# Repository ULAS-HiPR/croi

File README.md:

# Croí

Croí is the core flight-computer node in [Ogma](https://sean-osullivan.com/projects/ogma/), the University of Limerick Aeronautics Society's modular avionics stack for high-powered rocketry.

## Role

- Coordinates flight state across the 500 kbit/s CAN bus.
- Samples an LSM6DSO32 IMU and MS5607 barometer.
- Records flight data to SPI NOR flash.
- Runs on an STM32F072 and can operate as the stack's central logger.

## Repository

- `hardware/` - KiCad design and manufacturing outputs.
- `firmware/` - embedded firmware, peripheral probes, and tests.
- `schematics.png` - exported schematic overview.

## Status

Rev 1 firmware and hardware bring-up continue on [`ogma/flight-hardening`](https://github.com/ULAS-HiPR/croi/tree/ogma/flight-hardening). Release-candidate firmware builds and software tests pass, but hardware-in-the-loop validation is still underway. Croí is not yet flight-proven.

## Manufacturing support

Rev 1 PCB fabrication was sponsored through [EasyEDA Education](https://easyeda.com/education) and manufactured by [JLCPCB](https://jlcpcb.com/). The board was designed in KiCad and imported into EasyEDA Pro for the sponsorship and manufacturing workflow.

## More information

See the [Ogma project write-up](https://sean-osullivan.com/projects/ogma/) for the complete stack, bring-up work, and current status.

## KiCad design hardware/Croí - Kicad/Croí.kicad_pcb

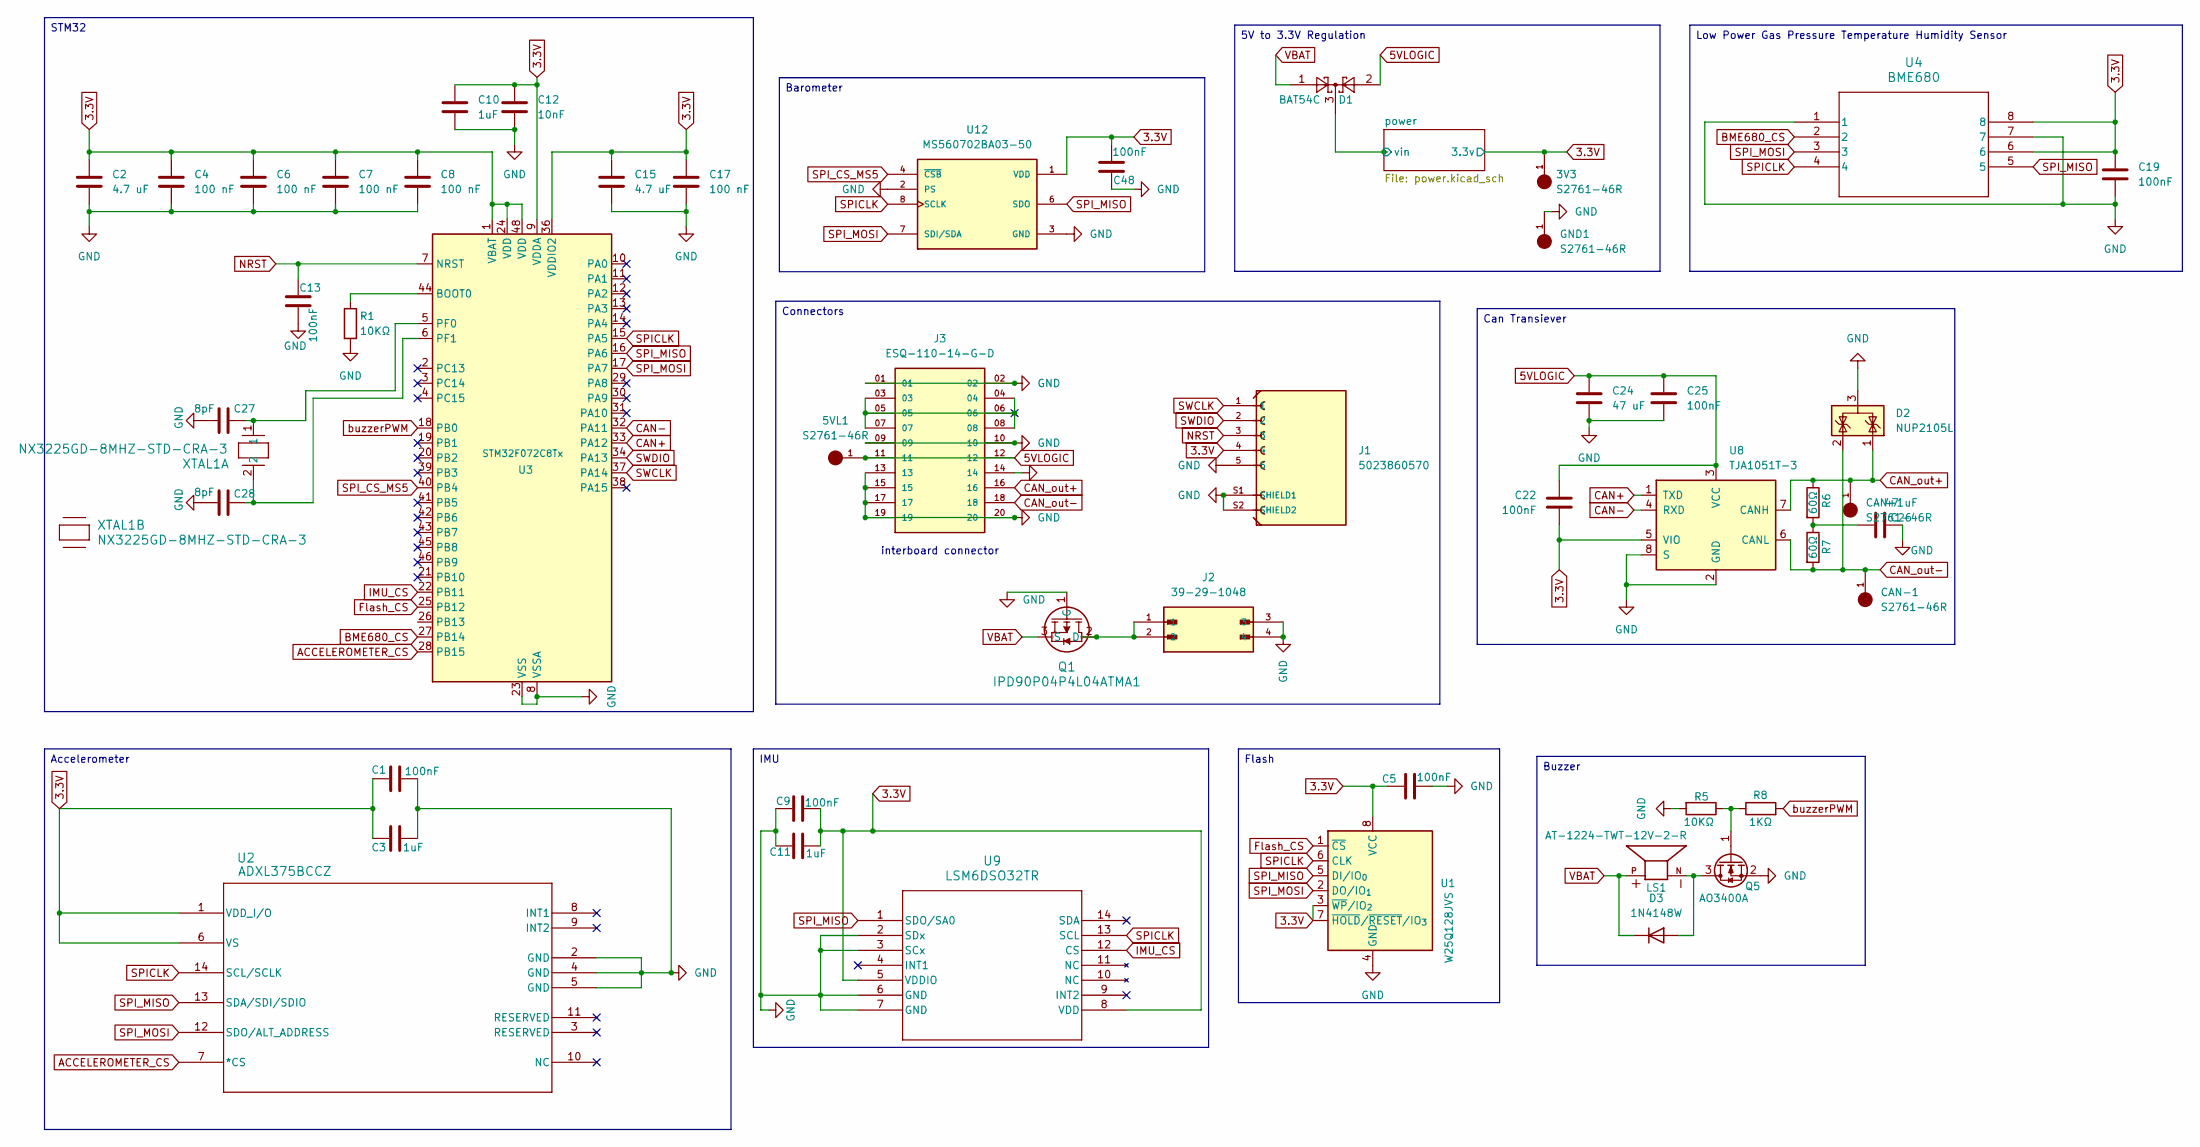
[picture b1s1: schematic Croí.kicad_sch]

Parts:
3V3, 5VL1: S2761-46R; HARWIN_S2761-46R; PARTREV 1
C1, C5, C9, C13, C19, C22, C25: 100nF; C_0402_1005Metric
C2, C15: 4.7 uF; C_0402_1005Metric
C3, C10, C11: 1uF; C_0402_1005Metric
C4, C6, C7, C8, C17: 100 nF; C_0402_1005Metric
C12: 10nF; C_0603_1608Metric
C24, C26: 47 uF; C_0603_1608Metric
C27, C28: 8pF; C_0402_1005Metric
C48: 100nF; R_0402_1005Metric
CAN+1: S2761-46R; HARWIN_S2761-46R; PARTREV 1
CAN-1: S2761-46R; HARWIN_S2761-46R; PARTREV 1
D1: BAT54C; SOT-23
D2: NUP2105L; SOT-23
D3: 1N4148W; D_SOD-123
GND1: S2761-46R; HARWIN_S2761-46R; PARTREV 1
J1: 5023860570; MOLEX_5023860570; PARTREV F
J2: 39-29-1048; MOLEX_39-29-1048
J3: ESQ-110-14-G-D; SAMTEC_ESQ-110-14-G-D; PARTREV NA
LS1: AT-1224-TWT-12V-2-R; XDCR_AT-1224-TWT-12V-2-R; PARTREV 2014/07/25
Q1: IPD90P04P4L04ATMA1; PG-TO252-3-313_INF
Q5: AO3400A; SOT-23
R1, R5: 10KΩ; R_0402_1005Metric
R6, R7: 60Ω; R_0402_1005Metric
R8: 1KΩ; R_0402_1005Metric
U1: W25Q128JVS; SOIC-8_5.3x5.3mm_P1.27mm
U2: ADXL375BCCZ; LGA_CC-14-1_ADI
U3: STM32F072C8Tx; LQFP-48_7x7mm_P0.5mm
U4: BME680; LGA8_BME680_BOS
U8: TJA1051T-3; SOIC-8_3.9x4.9mm_P1.27mm
U9: LSM6DSO32TR; LGA-14L_2P5X3X0P83_STM
U12: MS560702BA03-50; SON125P300X500X100-8N
XTAL1: NX3225GD-8MHZ-STD-CRA-3; XTAL_NX3225GD-8MHZ-STD-CRA-3_NDK

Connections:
3.3V: 3V3.1, C1.1, C2.1, C3.1, C4.1, C5.1, C6.1, C7.1, C8.1, C9.2, C10.1, C11.2, C12.1, C15.1, C17.1, C19.1, C22.1, C48.2, J1.4, U1.3 (~WP/IO_{2}), U1.7 (~HOLD/~RESET/IO_{3}), U1.8 (VCC), U2.1 (VDD_I/O), U2.6 (VS), U3.1 (VBAT), U3.9 (VDDA), U3.24 (VDD), U3.36 (VDDIO2), U3.48 (VDD), U4.6, U4.8, U8.5 (VIO), U9.5 (VDDIO), U9.8 (VDD), U12.1 (VDD); also elsewhere on the board
5VLOGIC: 5VL1.1, C22.2, C24.1, C25.1, D1.2, J3.11, J3.12, U8.3 (VCC); also elsewhere on the board
/power/vin: D1.3; also elsewhere on the board
ACCELEROMETER_CS: U2.7 (*CS), U3.28 (PB15)
BME680_CS: U3.27 (PB14), U4.2
CAN+: U3.33 (PA12), U8.1 (TXD)
CAN-: U3.32 (PA11), U8.4 (RXD)
CAN_out+: CAN+1.1, D2.1 (K), J3.16, R6.1, U8.7 (CANH); also elsewhere on the board
CAN_out-: CAN-1.1, D2.2 (K), J3.18, R7.2, U8.6 (CANL)
Flash_CS: U1.1 (~CS), U3.25 (PB12)
GND: C1.2, C2.2, C3.2, C4.2, C5.2, C6.2, C7.2, C8.2, C9.1, C10.2, C11.1, C12.2, C13.2, C15.2, C17.2, C19.2, C24.2, C25.2, C26.2, C27.1, C28.2, C48.1, D2.3 (A), GND1.1, J1.5, J1.S1 (SHIELD1), J1.S2 (SHIELD2), J2.3, J2.4, J3.01, J3.02, J3.09, J3.10, J3.13, J3.14, J3.15, J3.17, J3.19, J3.20, Q1.1 (G), Q5.2 (S), R1.2, R5.2, U1.4 (GND), U2.2 (GND), U2.4 (GND), U2.5 (GND), U3.8 (VSSA), U3.23 (VSS), U3.35 (VSS), U3.47 (VSS), U4.1, U4.7, U8.2 (GND), U8.8 (S), U9.2 (SDx), U9.3 (SCx), U9.6 (GND), U9.7 (GND), U12.2 (PS), U12.3 (GND); also elsewhere on the board
IMU_CS: U3.22 (PB11), U9.12 (CS)
NRST: C13.1, J1.3, U3.7 (NRST)
unnamed: C26.1, R6.2, R7.1
unnamed: D3.2 (A), LS1.N, Q5.3 (D)
unnamed: J2.1, J2.2, Q1.2 (D)
unnamed: Q5.1 (G), R5.1, R8.1
unnamed: R1.1, U3.44 (BOOT0)
unnamed: C27.2, U3.5 (PF0), XTAL1.1
unnamed: C28.1, U3.6 (PF1), XTAL1.2
SPICLK: U1.6 (CLK), U2.14 (SCL/SCLK), U3.15 (PA5), U4.4, U9.13 (SCL), U12.8 (SCLK)
SPI_CS_MS5: U3.40 (PB4), U12.4 (~CSB), U12.5 (~CSB)
SPI_MISO: U1.5 (DI/IO_{0}), U2.13 (SDA/SDI/SDIO), U3.16 (PA6), U4.5, U9.1 (SDO/SA0), U12.6 (SDO)
SPI_MOSI: U1.2 (DO/IO_{1}), U2.12 (SDO/ALT_ADDRESS), U3.17 (PA7), U4.3, U12.7 (SDI/SDA)
SWCLK: J1.1, U3.37 (PA14)
SWDIO: J1.2, U3.34 (PA13)
VBAT: D1.1, D3.1 (K), LS1.P, Q1.3 (S)
buzzerPWM: R8.2, U3.18 (PB0)

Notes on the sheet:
interboard connector
Low Power Gas Pressure Temperature Humidity Sensor
Can Transiever
Buzzer
Barometer
Flash
5V to 3.3V Regulation
Accelerometer
IMU
STM32
Connectors

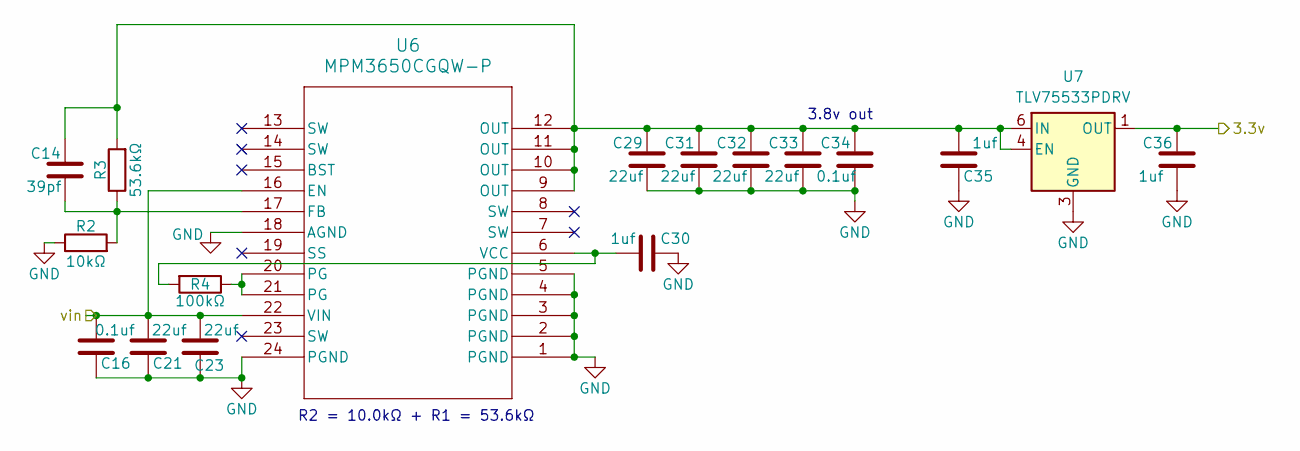
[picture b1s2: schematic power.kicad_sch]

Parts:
C14: 39pf; C_0402_1005Metric
C16, C34: 0.1uf; C_0402_1005Metric
C21, C23, C29, C31, C32, C33: 22uf; C_0603_1608Metric
C30, C35, C36: 1uf; C_0402_1005Metric
R2: 10kΩ; R_0402_1005Metric
R3: 53.6kΩ; R_0402_1005Metric
R4: 100kΩ; R_0402_1005Metric
U6: MPM3650CGQW-P; QFN-24_MPM3650_MNP
U7: TLV75533PDRV; WSON-6-1EP_2x2mm_P0.65mm_EP1x1.6mm

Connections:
3.3V: C36.1, U7.1 (OUT); also elsewhere on the board
/power/vin: C16.2, C21.2, C23.2, U6.16 (EN), U6.22 (VIN); also elsewhere on the board
GND: C16.1, C21.1, C23.1, C29.2, C30.1, C31.2, C32.2, C33.2, C34.2, C35.1, C36.2, R2.1, U6.1 (PGND), U6.2 (PGND), U6.3 (PGND), U6.4 (PGND), U6.5 (PGND), U6.18 (AGND), U6.24 (PGND), U7.3 (GND), U7.7 (GND); also elsewhere on the board
unnamed: R4.1, U6.20 (PG), U6.21 (PG)
unnamed: C14.2, R2.2, R3.1, U6.17 (FB)
unnamed: C30.2, R4.2, U6.6 (VCC)
unnamed: C14.1, C29.1, C31.1, C32.1, C33.1, C34.1, C35.2, R3.2, U6.9 (OUT), U6.10 (OUT), U6.11 (OUT), U6.12 (OUT), U7.4 (EN), U7.6 (IN)

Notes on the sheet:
3.8v out
R2 = 10.0kΩ + R1 = 53.6kΩ

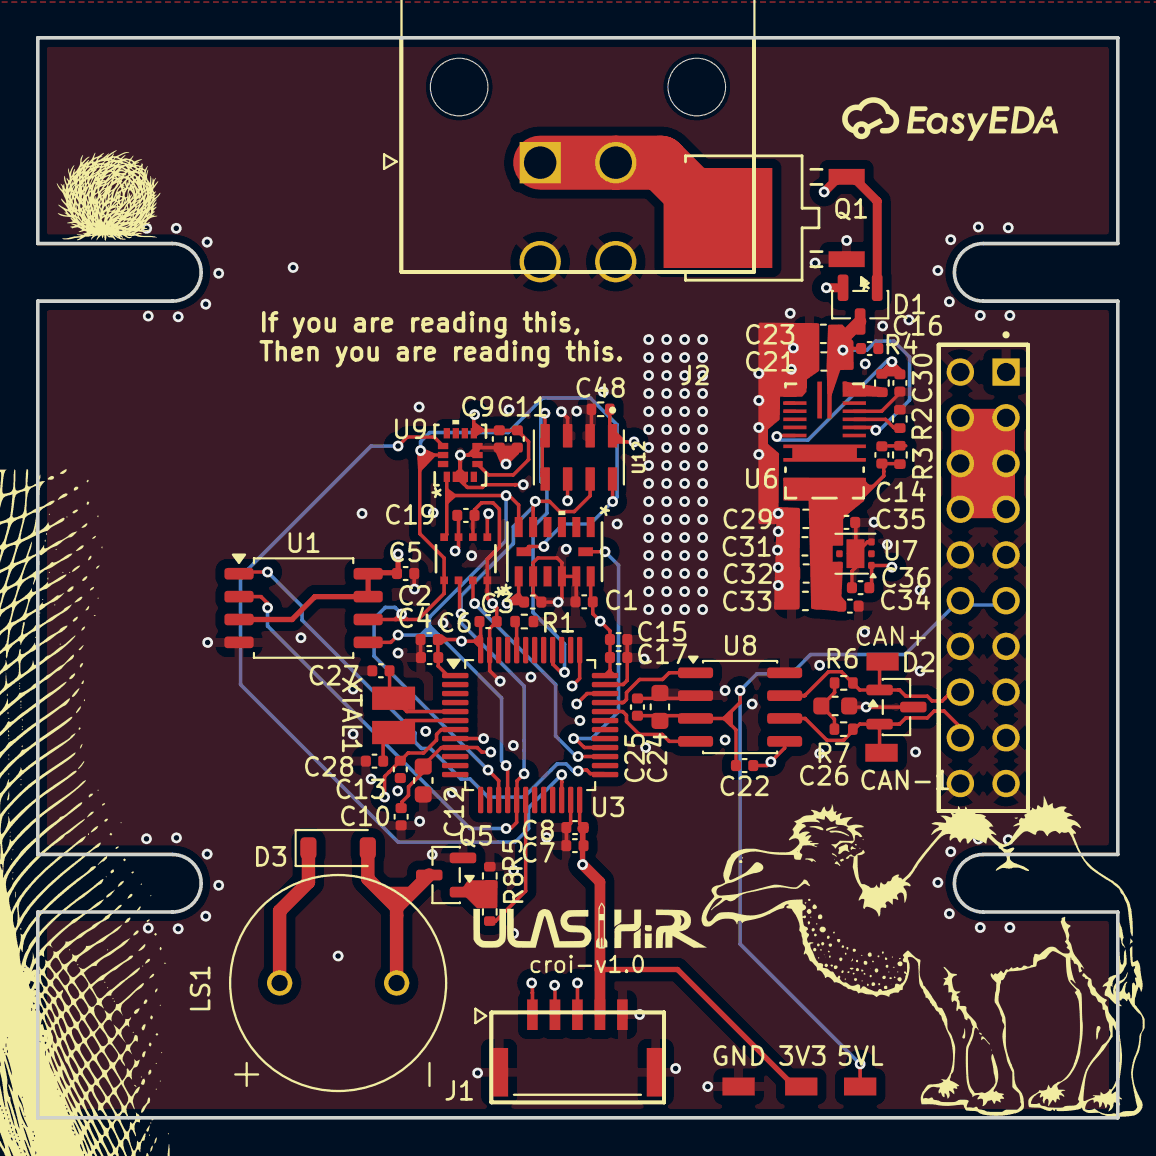
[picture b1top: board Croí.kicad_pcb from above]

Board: 6 copper layers, 60.0 x 60.0 mm, 67 parts (0 on the bottom side), 32 nets.

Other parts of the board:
5VL: S2761-46R; HARWIN_S2761-46R
CAN+: S2761-46R; HARWIN_S2761-46R
GND: S2761-46R; HARWIN_S2761-46R

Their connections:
5VLOGIC: 5VL.1; also elsewhere on the board
CAN_out+: CAN+.1; also elsewhere on the board
GND: GND.1; also elsewhere on the board

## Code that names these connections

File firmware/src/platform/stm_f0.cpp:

#if F0
#include "stm_f0.h"


CAN_HandleTypeDef hcan;
SPI_HandleTypeDef hspi1;
TIM_HandleTypeDef htim3;

void HAL_MspInit(void)
{

  /* USER CODE BEGIN MspInit 0 */

  /* USER CODE END MspInit 0 */

  __HAL_RCC_SYSCFG_CLK_ENABLE();
  __HAL_RCC_PWR_CLK_ENABLE();

  /* System interrupt init*/
  /* PendSV_IRQn interrupt configuration */
  HAL_NVIC_SetPriority(PendSV_IRQn, 3, 0);

  /* USER CODE BEGIN MspInit 1 */

  /* USER CODE END MspInit 1 */
}



/**
  * @brief CAN Initialization Function
  * @param None
  * @retval None
  */
void MX_CAN_Init(void)
{

  /* USER CODE BEGIN CAN_Init 0 */

  /* USER CODE END CAN_Init 0 */

  /* USER CODE BEGIN CAN_Init 1 */

  /* USER CODE END CAN_Init 1 */
  hcan.Instance = CAN;
  hcan.Init.Prescaler = 6;
  //hcan.Init.Mode = CAN_MODE_LOOPBACK;
  hcan.Init.Mode = CAN_MODE_NORMAL;
  hcan.Init.SyncJumpWidth = CAN_SJW_1TQ;
  hcan.Init.TimeSeg1 = CAN_BS1_13TQ;
  hcan.Init.TimeSeg2 = CAN_BS2_2TQ;
  hcan.Init.TimeTriggeredMode = DISABLE;
  hcan.Init.AutoBusOff = ENABLE;
  hcan.Init.AutoWakeUp = DISABLE;
  hcan.Init.AutoRetransmission = ENABLE;
  hcan.Init.ReceiveFifoLocked = DISABLE;
  hcan.Init.TransmitFifoPriority = DISABLE;
  if (HAL_CAN_Init(&hcan) != HAL_OK)
  {
    Error_Handler();
  }
  /* USER CODE BEGIN CAN_Init 2 */

  /* USER CODE END CAN_Init 2 */

}


/**
  * @brief CAN MSP Initialization
  * This function configures the hardware resources used in this example
  * @param hcan: CAN handle pointer
  * @retval None
  */
void HAL_CAN_MspInit(CAN_HandleTypeDef* hcan)
{
  GPIO_InitTypeDef GPIO_InitStruct = {0};
  if(hcan->Instance==CAN)
  {
    /* USER CODE BEGIN CAN_MspInit 0 */

    /* USER CODE END CAN_MspInit 0 */
    /* Peripheral clock enable */
    __HAL_RCC_CAN1_CLK_ENABLE();

    __HAL_RCC_GPIOA_CLK_ENABLE();
    /**CAN GPIO Configuration
    PA11     ------> CAN_RX
    PA12     ------> CAN_TX
    */
    GPIO_InitStruct.Pin = GPIO_PIN_11|GPIO_PIN_12;
    GPIO_InitStruct.Mode = GPIO_MODE_AF_PP;
    GPIO_InitStruct.Pull = GPIO_NOPULL;
    GPIO_InitStruct.Speed = GPIO_SPEED_FREQ_HIGH;
    GPIO_InitStruct.Alternate = GPIO_AF4_CAN;
    HAL_GPIO_Init(GPIOA, &GPIO_InitStruct);

    /* USER CODE BEGIN CAN_MspInit 1 */

    /* USER CODE END CAN_MspInit 1 */

  }

}

/**
  * @brief CAN MSP De-Initialization
  * This function freeze the hardware resources used in this example
  * @param hcan: CAN handle pointer
  * @retval None
  */
void HAL_CAN_MspDeInit(CAN_HandleTypeDef* hcan)
{
  if(hcan->Instance==CAN)
  {
    /* USER CODE BEGIN CAN_MspDeInit 0 */

    /* USER CODE END CAN_MspDeInit 0 */
    /* Peripheral clock disable */
    __HAL_RCC_CAN1_CLK_DISABLE();

    /**CAN GPIO Configuration
    PA11     ------> CAN_RX
    PA12     ------> CAN_TX
    */
    HAL_GPIO_DeInit(GPIOA, GPIO_PIN_11|GPIO_PIN_12);

    /* USER CODE BEGIN CAN_MspDeInit 1 */

    /* USER CODE END CAN_MspDeInit 1 */
  }

}

void MX_SPI1_Init(void)
{

  /* USER CODE BEGIN SPI1_Init 0 */

  /* USER CODE END SPI1_Init 0 */

  /* USER CODE BEGIN SPI1_Init 1 */

  /* USER CODE END SPI1_Init 1 */
  /* SPI1 parameter configuration*/
  hspi1.Instance = SPI1;
  hspi1.Init.Mode = SPI_MODE_MASTER;
  hspi1.Init.Direction = SPI_DIRECTION_2LINES;
  hspi1.Init.DataSize = SPI_DATASIZE_8BIT;
  hspi1.Init.CLKPolarity = SPI_POLARITY_LOW;
  hspi1.Init.CLKPhase = SPI_PHASE_1EDGE;
  hspi1.Init.NSS = SPI_NSS_SOFT;
  hspi1.Init.BaudRatePrescaler = SPI_BAUDRATEPRESCALER_8;
  hspi1.Init.FirstBit = SPI_FIRSTBIT_MSB;
  hspi1.Init.TIMode = SPI_TIMODE_DISABLE;
  hspi1.Init.CRCCalculation = SPI_CRCCALCULATION_DISABLE;

  if (HAL_SPI_Init(&hspi1) != HAL_OK)
  {
    Error_Handler();
  }
  /* USER CODE BEGIN SPI1_Init 2 */

  /* USER CODE END SPI1_Init 2 */

}


void HAL_SPI_MspInit(SPI_HandleTypeDef* hspi)
{
    if (hspi->Instance != SPI1) {
        return;
    }

    SPI_GPIO_CLK_ENABLE();
    FLASH_CS_GPIO_CLK_ENABLE();
    __HAL_RCC_SPI1_CLK_ENABLE();

    GPIO_InitTypeDef GPIO_InitStruct = {0};
    GPIO_InitStruct.Pin = SPI_SCK_PIN | SPI_MISO_PIN | SPI_MOSI_PIN;
    GPIO_InitStruct.Mode = GPIO_MODE_AF_PP;
    GPIO_InitStruct.Pull = GPIO_NOPULL;
    GPIO_InitStruct.Speed = GPIO_SPEED_FREQ_HIGH;
    GPIO_InitStruct.Alternate = GPIO_AF0_SPI1;
    HAL_GPIO_Init(SPI_GPIO_PORT, &GPIO_InitStruct);

    GPIO_InitStruct.Pin = BARO_CS_PIN |
                           IMU_CS_PIN |
                           FLASH_CS_PIN |
                           BME680_CS_PIN |
                           ADXL375_CS_PIN;
    GPIO_InitStruct.Mode = GPIO_MODE_OUTPUT_PP;
    GPIO_InitStruct.Pull = GPIO_NOPULL;
    GPIO_InitStruct.Speed = GPIO_SPEED_FREQ_HIGH;
    HAL_GPIO_Init(GPIOB, &GPIO_InitStruct);
    HAL_GPIO_WritePin(BARO_CS_PORT, BARO_CS_PIN, GPIO_PIN_SET);
    HAL_GPIO_WritePin(IMU_CS_PORT, IMU_CS_PIN, GPIO_PIN_SET);
    HAL_GPIO_WritePin(FLASH_CS_PORT, FLASH_CS_PIN, GPIO_PIN_SET);
    HAL_GPIO_WritePin(BME680_CS_PORT, BME680_CS_PIN, GPIO_PIN_SET);
    HAL_GPIO_WritePin(ADXL375_CS_PORT, ADXL375_CS_PIN, GPIO_PIN_SET);
}

/**
  * @brief SPI MSP De-Initialization
  * This function freeze the hardware resources used in this example
  * @param hspi: SPI handle pointer
  * @retval None
  */
void HAL_SPI_MspDeInit(SPI_HandleTypeDef* hspi)
{
  if(hspi->Instance==SPI1)
  {
    /* USER CODE BEGIN SPI1_MspDeInit 0 */

    /* USER CODE END SPI1_MspDeInit 0 */
    /* Peripheral clock disable */
    __HAL_RCC_SPI1_CLK_DISABLE();

    /**SPI1 GPIO Configuration
    PA5     ------> SPI1_SCK
    PA6     ------> SPI1_MISO
    PA7     ------> SPI1_MOSI
    */
    HAL_GPIO_DeInit(GPIOA, GPIO_PIN_5|GPIO_PIN_6|GPIO_PIN_7 | BARO_CS_PIN | IMU_CS_PIN | FLASH_CS_PIN | BME680_CS_PIN | ADXL375_CS_PIN);

    /* USER CODE BEGIN SPI1_MspDeInit 1 */

    /* USER CODE END SPI1_MspDeInit 1 */
  }

}

/**
  * @brief GPIO Initialization Function
  * @param None
  * @retval None
  */
void MX_GPIO_Init(void)
{
  GPIO_InitTypeDef GPIO_InitStruct = {0};
  /* USER CODE BEGIN MX_GPIO_Init_1 */

  /* USER CODE END MX_GPIO_Init_1 */

  /* GPIO Ports Clock Enable */
  __HAL_RCC_GPIOA_CLK_ENABLE();
  __HAL_RCC_GPIOB_CLK_ENABLE();

  /*Configure GPIO pin Output Level */
  //HAL_GPIO_WritePin(GPIOB, GPIO_PIN_0| GPIO_PIN_RESET);

  /*Configure GPIO pins : PB0 IMU_CS_Pin FLASH_CS_Pin BME_CS_Pin
                           ADXL_CS_Pin BARO_CS_Pin */
  GPIO_InitStruct.Pin = GPIO_PIN_0;
  GPIO_InitStruct.Mode = GPIO_MODE_OUTPUT_PP;
  GPIO_InitStruct.Pull = GPIO_NOPULL;
  GPIO_InitStruct.Speed = GPIO_SPEED_FREQ_LOW;
  HAL_GPIO_Init(GPIOB, &GPIO_InitStruct);

  /* USER CODE BEGIN MX_GPIO_Init_2 */

  /* USER CODE END MX_GPIO_Init_2 */
}

void HAL_TIM_PWM_MspInit(TIM_HandleTypeDef* htim)
{
    if (htim->Instance == TIM3) {
        __HAL_RCC_TIM3_CLK_ENABLE();
    }
}

void HAL_TIM_MspPostInit(TIM_HandleTypeDef* htim)
{
    if (htim->Instance != TIM3) {
        return;
    }

    __HAL_RCC_GPIOB_CLK_ENABLE();

    GPIO_InitTypeDef gpio = {0};
    gpio.Pin = BUZZER_GPIO_PIN;
    gpio.Mode = GPIO_MODE_AF_PP;
    gpio.Pull = GPIO_NOPULL;
    gpio.Speed = GPIO_SPEED_FREQ_HIGH;
    gpio.Alternate = GPIO_AF1_TIM3;
    HAL_GPIO_Init(BUZZER_GPIO_PORT, &gpio);
}



void MX_TIM3_Init(void)
{
    TIM_OC_InitTypeDef config = {0};

    uint32_t timer_clock = HAL_RCC_GetPCLK1Freq();
    uint32_t prescaler = timer_clock / BUZZER_TIMER_TICK_HZ;
    if (prescaler == 0U) {
        prescaler = 1U;
    }

    htim3.Instance = TIM3;
    htim3.Init.Prescaler = prescaler - 1U;
    htim3.Init.CounterMode = TIM_COUNTERMODE_UP;
    htim3.Init.Period = 1000U - 1U;
    htim3.Init.ClockDivision = TIM_CLOCKDIVISION_DIV1;
    htim3.Init.AutoReloadPreload = TIM_AUTORELOAD_PRELOAD_DISABLE;

    if (HAL_TIM_PWM_Init(&htim3) != HAL_OK) {
        Error_Handler();
    }

    config.OCMode = TIM_OCMODE_PWM1;
    config.Pulse = 0;
    config.OCPolarity = TIM_OCPOLARITY_HIGH;
    config.OCFastMode = TIM_OCFAST_DISABLE;

    if (HAL_TIM_PWM_ConfigChannel(&htim3, &config, TIM_CHANNEL_3) != HAL_OK) {
        Error_Handler();
    }

    HAL_TIM_MspPostInit(&htim3);

    if (HAL_TIM_PWM_Start(&htim3, TIM_CHANNEL_3) != HAL_OK) {
        Error_Handler();
    }

    if (htim3.Instance != nullptr) {
        __HAL_TIM_SET_COMPARE(&htim3, TIM_CHANNEL_3, 0);
    }
}
#endif // F0

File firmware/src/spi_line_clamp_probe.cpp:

#include "stm32f0xx.h"

#include <cstdint>

namespace {

constexpr std::uint32_t kSysClockHz = 48000000U;
constexpr std::uint32_t kTimerTickHz = 1000000U;

constexpr std::uint16_t kSck = 1U << 5U;       // PA5
constexpr std::uint16_t kMisoNet = 1U << 6U;   // PA6
constexpr std::uint16_t kMosiNet = 1U << 7U;   // PA7
constexpr std::uint16_t kBuzzer = 1U << 0U;    // PB0
constexpr std::uint16_t kBaroCs = 1U << 4U;    // PB4
constexpr std::uint16_t kImuCs = 1U << 11U;    // PB11
constexpr std::uint16_t kFlashCs = 1U << 12U;  // PB12
constexpr std::uint16_t kBme680Cs = 1U << 14U; // PB14
constexpr std::uint16_t kAdxl375Cs = 1U << 15U;// PB15
constexpr std::uint16_t kAllCs = kBaroCs | kImuCs | kFlashCs | kBme680Cs | kAdxl375Cs;

void pin_high(GPIO_TypeDef* port, std::uint16_t pin)
{
    port->BSRR = pin;
}

void pin_low(GPIO_TypeDef* port, std::uint16_t pin)
{
    port->BRR = pin;
}

void clock_init()
{
    RCC->CR2 |= RCC_CR2_HSI48ON;
    while ((RCC->CR2 & RCC_CR2_HSI48RDY) == 0U) {}

    FLASH->ACR |= FLASH_ACR_LATENCY;

    RCC->CFGR &= ~RCC_CFGR_SW;
    RCC->CFGR |= RCC_CFGR_SW_HSI48;
    while ((RCC->CFGR & RCC_CFGR_SWS) != RCC_CFGR_SWS_HSI48) {}
}

void timebase_init()
{
    RCC->APB1ENR |= RCC_APB1ENR_TIM3EN;
    (void)RCC->APB1ENR;

    TIM3->PSC = (kSysClockHz / kTimerTickHz) - 1U;
    TIM3->ARR = 0xFFFFU;
    TIM3->EGR = TIM_EGR_UG;
    TIM3->CR1 = TIM_CR1_CEN;
}

void delay_us(std::uint32_t us)
{
    while (us > 0U) {
        const std::uint32_t chunk = us > 60000U ? 60000U : us;
        TIM3->CNT = 0U;
        while (TIM3->CNT < chunk) {}
        us -= chunk;
    }
}

void delay_ms(std::uint32_t ms)
{
    while (ms-- > 0U) {
        delay_us(1000U);
    }
}

void beep(std::uint16_t frequency_hz, std::uint16_t duration_ms)
{
    const std::uint32_t half_period_us = 500000UL / frequency_hz;
    const std::uint32_t total_us = static_cast<std::uint32_t>(duration_ms) * 1000U;
    std::uint32_t elapsed_us = 0U;

    while ((elapsed_us + (half_period_us * 2U)) <= total_us) {
        pin_high(GPIOB, kBuzzer);
        delay_us(half_period_us);
        pin_low(GPIOB, kBuzzer);
        delay_us(half_period_us);
        elapsed_us += half_period_us * 2U;
    }

    pin_low(GPIOB, kBuzzer);
}

void rest(std::uint16_t ms)
{
    pin_low(GPIOB, kBuzzer);
    delay_ms(ms);
}

void marker(std::uint8_t count)
{
    rest(600U);
    for (std::uint8_t i = 0U; i < count; ++i) {
        beep(1047U, 90U);
        rest(110U);
    }
    rest(350U);
}

void gpio_init()
{
    RCC->AHBENR |= RCC_AHBENR_GPIOAEN | RCC_AHBENR_GPIOBEN;
    (void)RCC->AHBENR;

    GPIOB->MODER &= ~((3UL << (0U * 2U)) |
                      (3UL << (4U * 2U)) |
                      (3UL << (11U * 2U)) |
                      (3UL << (12U * 2U)) |
                      (3UL << (14U * 2U)) |
                      (3UL << (15U * 2U)));
    GPIOB->MODER |= (1UL << (0U * 2U)) |
                    (1UL << (4U * 2U)) |
                    (1UL << (11U * 2U)) |
                    (1UL << (12U * 2U)) |
                    (1UL << (14U * 2U)) |
                    (1UL << (15U * 2U));
    GPIOB->OTYPER &= ~(kBuzzer | kAllCs);
    GPIOB->PUPDR &= ~((3UL << (0U * 2U)) |
                      (3UL << (4U * 2U)) |
                      (3UL << (11U * 2U)) |
                      (3UL << (12U * 2U)) |
                      (3UL << (14U * 2U)) |
                      (3UL << (15U * 2U)));
    GPIOB->OSPEEDR |= (3UL << (0U * 2U)) |
                      (3UL << (4U * 2U)) |
                      (3UL << (11U * 2U)) |
                      (3UL << (12U * 2U)) |
                      (3UL << (14U * 2U)) |
                      (3UL << (15U * 2U));

    GPIOA->MODER &= ~((3UL << (5U * 2U)) |
                      (3UL << (6U * 2U)) |
                      (3UL << (7U * 2U)));
    GPIOA->MODER |= (1UL << (5U * 2U)) |
                    (1UL << (6U * 2U)) |
                    (1UL << (7U * 2U));
    GPIOA->OTYPER &= ~(kSck | kMisoNet | kMosiNet);
    GPIOA->PUPDR &= ~((3UL << (5U * 2U)) |
                      (3UL << (6U * 2U)) |
                      (3UL << (7U * 2U)));
    GPIOA->OSPEEDR |= (3UL << (5U * 2U)) |
                      (3UL << (6U * 2U)) |
                      (3UL << (7U * 2U));

    pin_high(GPIOB, kAllCs);
    pin_low(GPIOB, kBuzzer);
    GPIOA->BRR = kSck | kMisoNet | kMosiNet;
}

void set_lines(bool sck, bool miso, bool mosi)
{
    pin_high(GPIOB, kAllCs);

    if (sck) {
        pin_high(GPIOA, kSck);
    } else {
        pin_low(GPIOA, kSck);
    }

    if (miso) {
        pin_high(GPIOA, kMisoNet);
    } else {
        pin_low(GPIOA, kMisoNet);
    }

    if (mosi) {
        pin_high(GPIOA, kMosiNet);
    } else {
        pin_low(GPIOA, kMosiNet);
    }
}

void hold_section(std::uint8_t count, bool sck, bool miso, bool mosi)
{
    set_lines(false, false, false);
    marker(count);
    set_lines(sck, miso, mosi);
    delay_ms(2500U);
    set_lines(false, false, false);
}

void toggle_section(std::uint8_t count, bool toggle_miso, bool toggle_mosi)
{
    set_lines(false, false, false);
    marker(count);

    for (std::uint16_t i = 0U; i < 80U; ++i) {
        set_lines(false, toggle_miso, toggle_mosi);
        delay_ms(25U);
        set_lines(false, false, false);
        delay_ms(25U);
    }
}

} // namespace

int main()
{
    clock_init();
    gpio_init();
    timebase_init();

    beep(523U, 100U);
    rest(60U);
    beep(784U, 100U);
    rest(60U);
    beep(1047U, 140U);

    while (true) {
        hold_section(1U, false, false, true); // PA7 / MOSI high, all CS high.
        hold_section(2U, false, true, false); // PA6 / MISO high, all CS high.
        hold_section(3U, false, true, true);  // Both data lines high, all CS high.
        hold_section(4U, true, false, false); // PA5 / SCK high, all CS high.
        toggle_section(5U, false, true);      // PA7 / MOSI square wave, all CS high.
        toggle_section(6U, true, false);      // PA6 / MISO square wave, all CS high.
        toggle_section(7U, true, true);       // Both data lines square wave, all CS high.
        rest(1200U);
    }
}

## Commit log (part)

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2025-12-23 adding in base pio files
2025-12-23 setting up code -> i hate libraries
2026-01-06 libs are working now
2026-01-13 adding workflows & basic code
2026-01-13 adding readme
2026-01-14 First addition of Kicad project
2026-01-14 minor junctions
2026-01-14 did basically all of it
2026-01-14 started pcb work
2026-01-14 Finalised board with accelerometer and IMU
2026-01-14 readme added
2026-01-19 summaries are hard
2026-01-22 changed some stuff
2026-01-22 crazy work
2026-01-24 Board Routing completed: Ready for Review
2026-01-26 minor changes
2026-01-26 Memes added, Dervla might recognise someone
2026-01-27 major changes
2026-01-27 repositioned board
2026-01-28 random ass changes
2026-01-29 Crazy new changes
2026-01-29 cleaning up: should be near done now
2026-01-30 cleaned up
2026-01-31 cleaned up a trace
2026-02-03 3d model made
2026-02-07 Started Applying Global Changes
    1. Shape and screwholes
    2. Mosfet
    3. New Molex
2026-02-10 Only missing one thing off the notion i believe, all 3d modlels should work
2026-02-11 lots left to do, but good enough for render
2026-02-13 base compiling with static analysis
2026-02-13 adding base software for an example, not working, fightin with eigen
2026-02-14 most issues solved, the thing i knew would cause issues not causing issues:
2026-02-14 updating pipeline
2026-02-16 running
2026-02-16 clean asf
2026-02-22 editing old magik code for poc
2026-02-22 Fix CI workflow for STM quality check and artifact path
2026-02-22 Update CI workflow to include SIL tests
2026-02-22 sil is working
2026-02-22 nucleo compiling yay
2026-02-22 getting rid of dumb comments
2026-02-22 Add verbose flag to test and check commands
    Updated test and quality check commands to include verbose output.
2026-02-22 fuck the compiler i hate this
2026-02-22 updating paths for cidi
2026-02-22 adding in deleted files
2026-02-23 literally changed nothing
2026-02-23 Removing fake static analysis errors
2026-02-23 ready for review the twost
2026-02-26 good to go
2026-02-26 fixed
2026-02-27 ready to go, nearly
2026-03-01 ready 2 order
2026-03-03 Minor naming & specifing gitmodules
2026-03-03 fixing git submodules
2026-03-03 Removing DS Store
2026-03-31 hardware done
2026-04-20 updated to f0
2026-04-20 syncing submodules
2026-04-20 updateing cidi
2026-04-20 forogt to add more files
2026-04-21 re ing fake static analysis errors
2026-04-21 adding common tasks & importing correct sensors
2026-04-21 fixed all build errors & added correct queues
2026-04-21 added a second can queue
2026-04-21 basic can stuff
2026-04-21 making state_machine task
2026-04-21 f0 version compiled
2026-04-21 renamed can
2026-04-22 Added updated Kalman filter
2026-05-07 progress, not flashing yet
2026-05-07 demo code working, issues with flashing
2026-05-18 feat(comheadan): update submodule
2026-05-18 feat(linux): platform for running on linux instead of target hw
2026-05-19 all bar bme are alive now
2026-05-27 fixed all compile errors
2026-05-27 updated kalman to all floats & fixed memory issue
2026-05-30 imu, baro and flash demo
2026-06-07 Correcting logging & can tasks
2026-06-10 fixing overall freeRTOS stuff - getting odd error
2026-06-22 fix: stripping back to isolate CAN
2026-06-23 test: add bare CAN hardware diagnostic
2026-06-23 feat: buzzer, imu & baro working in loops
2026-06-26 Integrate hardened CAN task
2026-06-26 stuff kinda working
2026-06-26 inital can intergration
2026-06-26 maybe works??
2026-06-26 fixing up stuff - locking down for now
2026-06-27 Integrate flash logger preflight gate
2026-06-27 Add SWD flash CSV readout task
2026-06-27 Chunk SWD flash CSV readout
2026-06-27 very basic logging workign
2026-06-29 final commit - i hope
2026-06-29 updating can branch stuff
